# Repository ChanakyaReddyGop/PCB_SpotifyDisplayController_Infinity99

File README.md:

# PCB_SpotifyDisplayController_Infinity99
A Spotify Display and Controller PCB using ESP32 and buttons for controls and a volume dial

## What is it?
A PCB that uses an ESP32 to display the currently playing Spotify song on a LCD screen. It takes inputs from three buttons for previous, pause, and skip, as well as a potentiometer for volume control 

## Current Status
PCB designed in KiCAD, simple stand made\
Firmware completed and uploaded\
Updates in [JOURNAL.md](https://github.com/ChanakyaReddyGop/PCB_SpotifyDisplayController_Infinity99/blob/main/JOURNAL.md)

## PCB
PCB files in [PCB](https://github.com/ChanakyaReddyGop/PCB_SpotifyDisplayController_Infinity99/tree/main/pcb)\
Drill and Gerber files in [gerber and drill.zip](https://github.com/ChanakyaReddyGop/PCB_SpotifyDisplayController_Infinity99/blob/main/pcb/gerber%20and%20drill.zip)\

## Firmware
ESP32 firmware in [SpotifyDisplayController](https://github.com/ChanakyaReddyGop/PCB_SpotifyDisplayController_Infinity99/tree/main/firmware/SpotifyDisplayController)\
Bridge code in [bridge.py](https://github.com/ChanakyaReddyGop/PCB_SpotifyDisplayController_Infinity99/blob/main/firmware/bridge.py)

## CAD
CAD Model of PCB and Simple Stand in [SpotifyDisplayCAD.step](https://github.com/ChanakyaReddyGop/PCB_SpotifyDisplayController_Infinity99/blob/main/cad/SpotifyDisplay%20CAD.step)

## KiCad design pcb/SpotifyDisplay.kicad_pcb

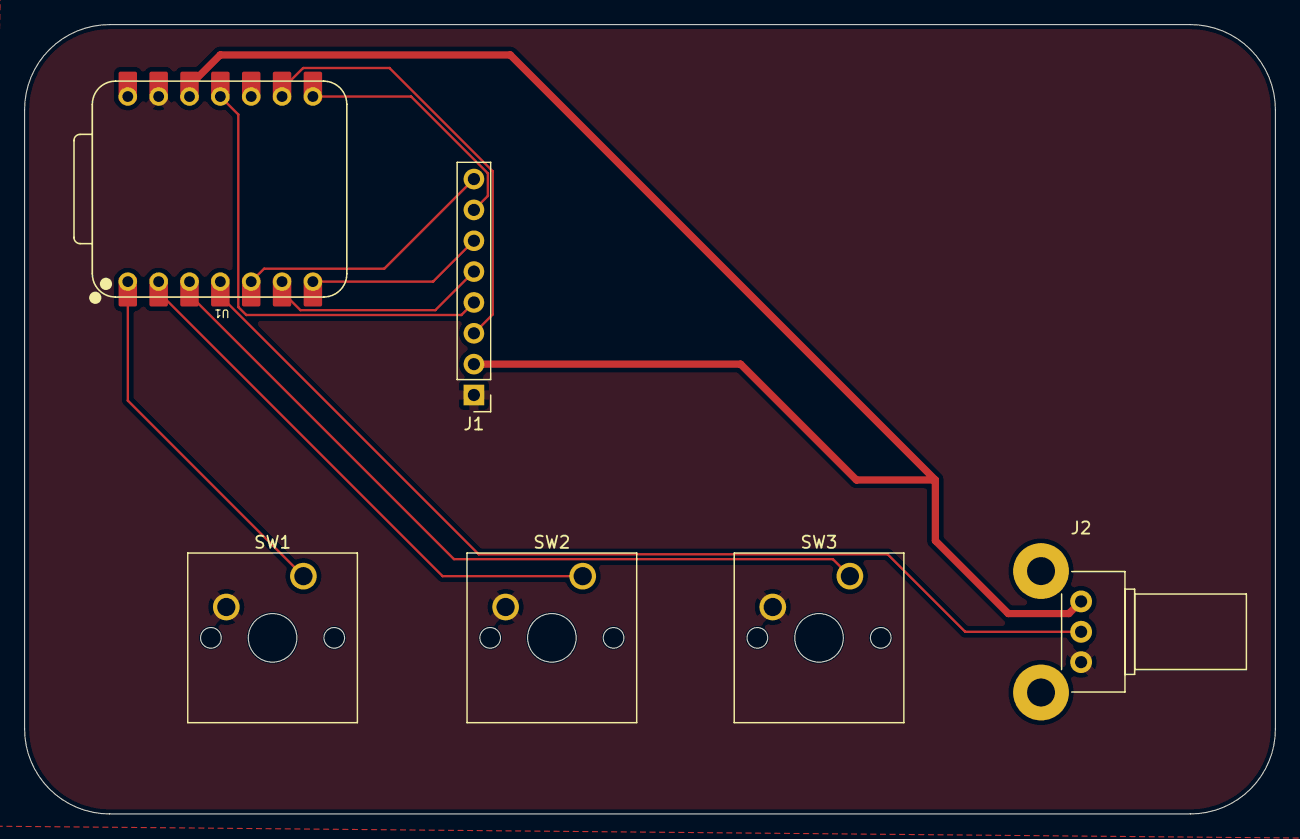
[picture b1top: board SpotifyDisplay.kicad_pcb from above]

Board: 2 copper layers, 103.0 x 65.0 mm, 6 parts (0 on the bottom side), 12 nets.

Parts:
J1: Conn_01x08_Pin; PinHeader_1x08_P2.54mm_Vertical
J2: Conn_01x03_Pin; Potentiometer_Bourns_PTV09A-2_Single_Horizontal
SW1, SW2, SW3: SW_Push; SW_Cherry_MX_1.00u_PCB
U1: XIAO-ESP32-C3-SMD; XIAO-ESP32-C6-DIP

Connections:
+3.3V: J1.2, J2.3, U1.12 (3V3_OUT)
/BL: J1.8, U1.5 (D4)
/CS: J1.7, U1.8 (D7)
/DC: J1.6, U1.7 (D6)
/GPIO0: SW1.1, U1.1 (D0)
/GPIO1: SW2.1, U1.2 (D1)
/GPIO2: SW3.1, U1.3 (D2)
/GPIO4: J2.2, U1.4 (D3)
/RES: J1.5, U1.6 (D5)
/SCL: J1.3, U1.9 (D8)
/SDA: J1.4, U1.11 (D10)
GND: J1.1, J2.1, SW1.2, SW2.2, SW3.2, U1.13 (GND)
